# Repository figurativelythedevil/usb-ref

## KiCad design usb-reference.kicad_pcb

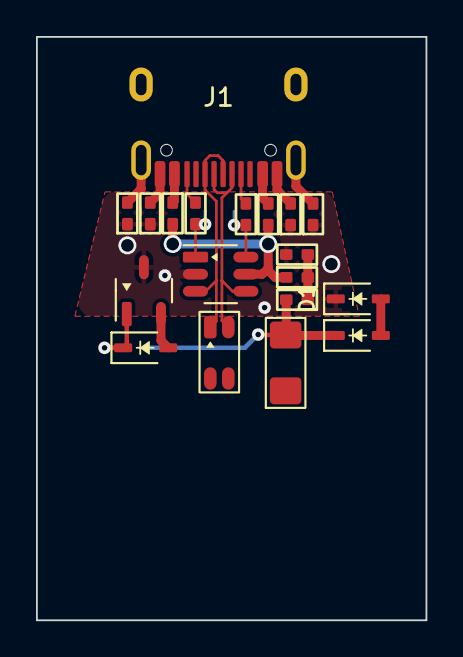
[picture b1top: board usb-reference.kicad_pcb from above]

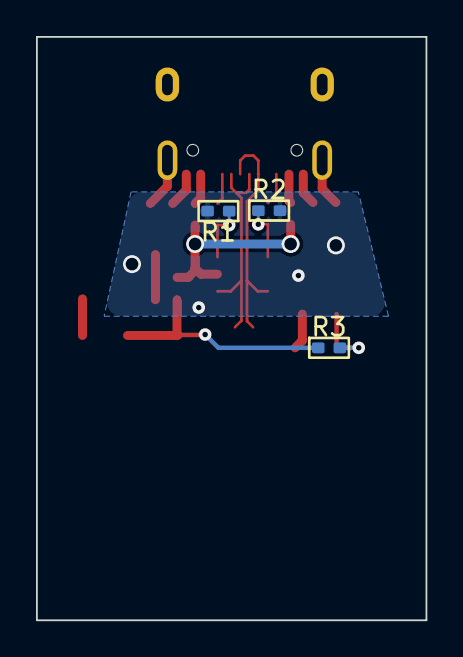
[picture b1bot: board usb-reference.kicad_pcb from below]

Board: 2 copper layers, 21.6 x 32.4 mm, 22 parts (3 on the bottom side), 18 nets.

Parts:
C1: 0.68uF; C_0402_1005Metric_Pad0.74x0.62mm_HandSolder
D1: NSR0340HT1G; D_SOD-323
F1: 1A Trip; Fuse_1206_3216Metric_Pad1.42x1.75mm_HandSolder
FB1, FB2, FB3, FB4, FB6, FB7, FB8, FB9, FB10, FB11: 600R @ 100MHz; R_0402_1005Metric_Pad0.72x0.64mm_HandSolder
J1: USB4085-GF-A; TYPE-C-31-M-12
L1: 90R @ 100MHz; CMC-WE-744232090
Q1: DMN2058UW-7; SOT-23
R1, R2: 5.1kΩ; R_0402_1005Metric_Pad0.72x0.64mm_HandSolder
R3: 10k; R_0402_1005Metric_Pad0.72x0.64mm_HandSolder
U1: 82400102; SOT-23-6_Handsoldering
Z1: 6.2V; D_SOD-323
Z2: 10V; D_SOD-323

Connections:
AGND: C1.2, D1.1 (K), FB1.1, FB2.1, FB3.1, FB4.1, Q1.3 (D), R1.2, R2.2, U1.2
DBUS+: J1.A6 (D+), J1.B6 (D+), L1.1, U1.3
DBUS-: J1.A7 (D-), J1.B7 (D-), L1.4, U1.4
GND: Q1.2 (S), Z2.2 (A)
unnamed: C1.1, FB10.2, FB11.1
unnamed: D1.2 (A), Z1.2 (A)
unnamed: FB3.2, J1.B1 (GND)
unnamed: FB4.2, J1.A1 (GND)
unnamed: FB6.1, J1.A4 (VBUS)
unnamed: FB7.1, J1.B4 (VBUS)
unnamed: FB8.2, R1.1, U1.6
unnamed: FB9.2, R2.1, U1.1
unnamed: FB8.1, J1.A5 (CC1)
unnamed: FB9.1, J1.B5 (CC2)
unnamed: Q1.1 (G), R3.2, Z2.1 (K)
unnamed: F1.2, FB11.2, R3.1, Z1.1 (K)
SHIELD: FB1.2, FB2.2, J1.S (SHIELD)
VBUS: FB6.2, FB7.2, FB10.1, U1.5
